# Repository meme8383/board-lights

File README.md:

# Meepo V3S ARGB Power & Control PCB
Schematic for Meepo V3S Skateboard Lights. Meant to power [these 24V WS2811 COB Leds](https://www.aliexpress.us/item/3256805848873454.html?gatewayAdapt=glo2usa) using the Meepo V3S 36V Battery and [wled firmware](https://kno.wled.ge/).

https://github.com/user-attachments/assets/10e10ca3-55f4-4bfa-9f18-f33567d93a93

## Known issues
This was my first real PCB project, so there were many (easily fixable) issues, but it still works as-is.
- Did not pull EN high (whoops). Bridge the two upper pins of the connector after the board is powered on.
- ESP-Prog connector is mirrored (whoops again).
- The output capacitor I planned to use did not support 24V. There is a capacitor with the same footprint and lower capacitance but higher max voltage that I used instead. Let me know if you want the full BOM.
- There is no power switch. I intented to use an inline waterproof switch on the connector, but it would have been nice to be able to disable the board without unplugging it or pulling the fuse.
- There are no holes (or space for them) to connect it to a mount.
- Level shifter did not work. I just bridged the pins and it works fine.

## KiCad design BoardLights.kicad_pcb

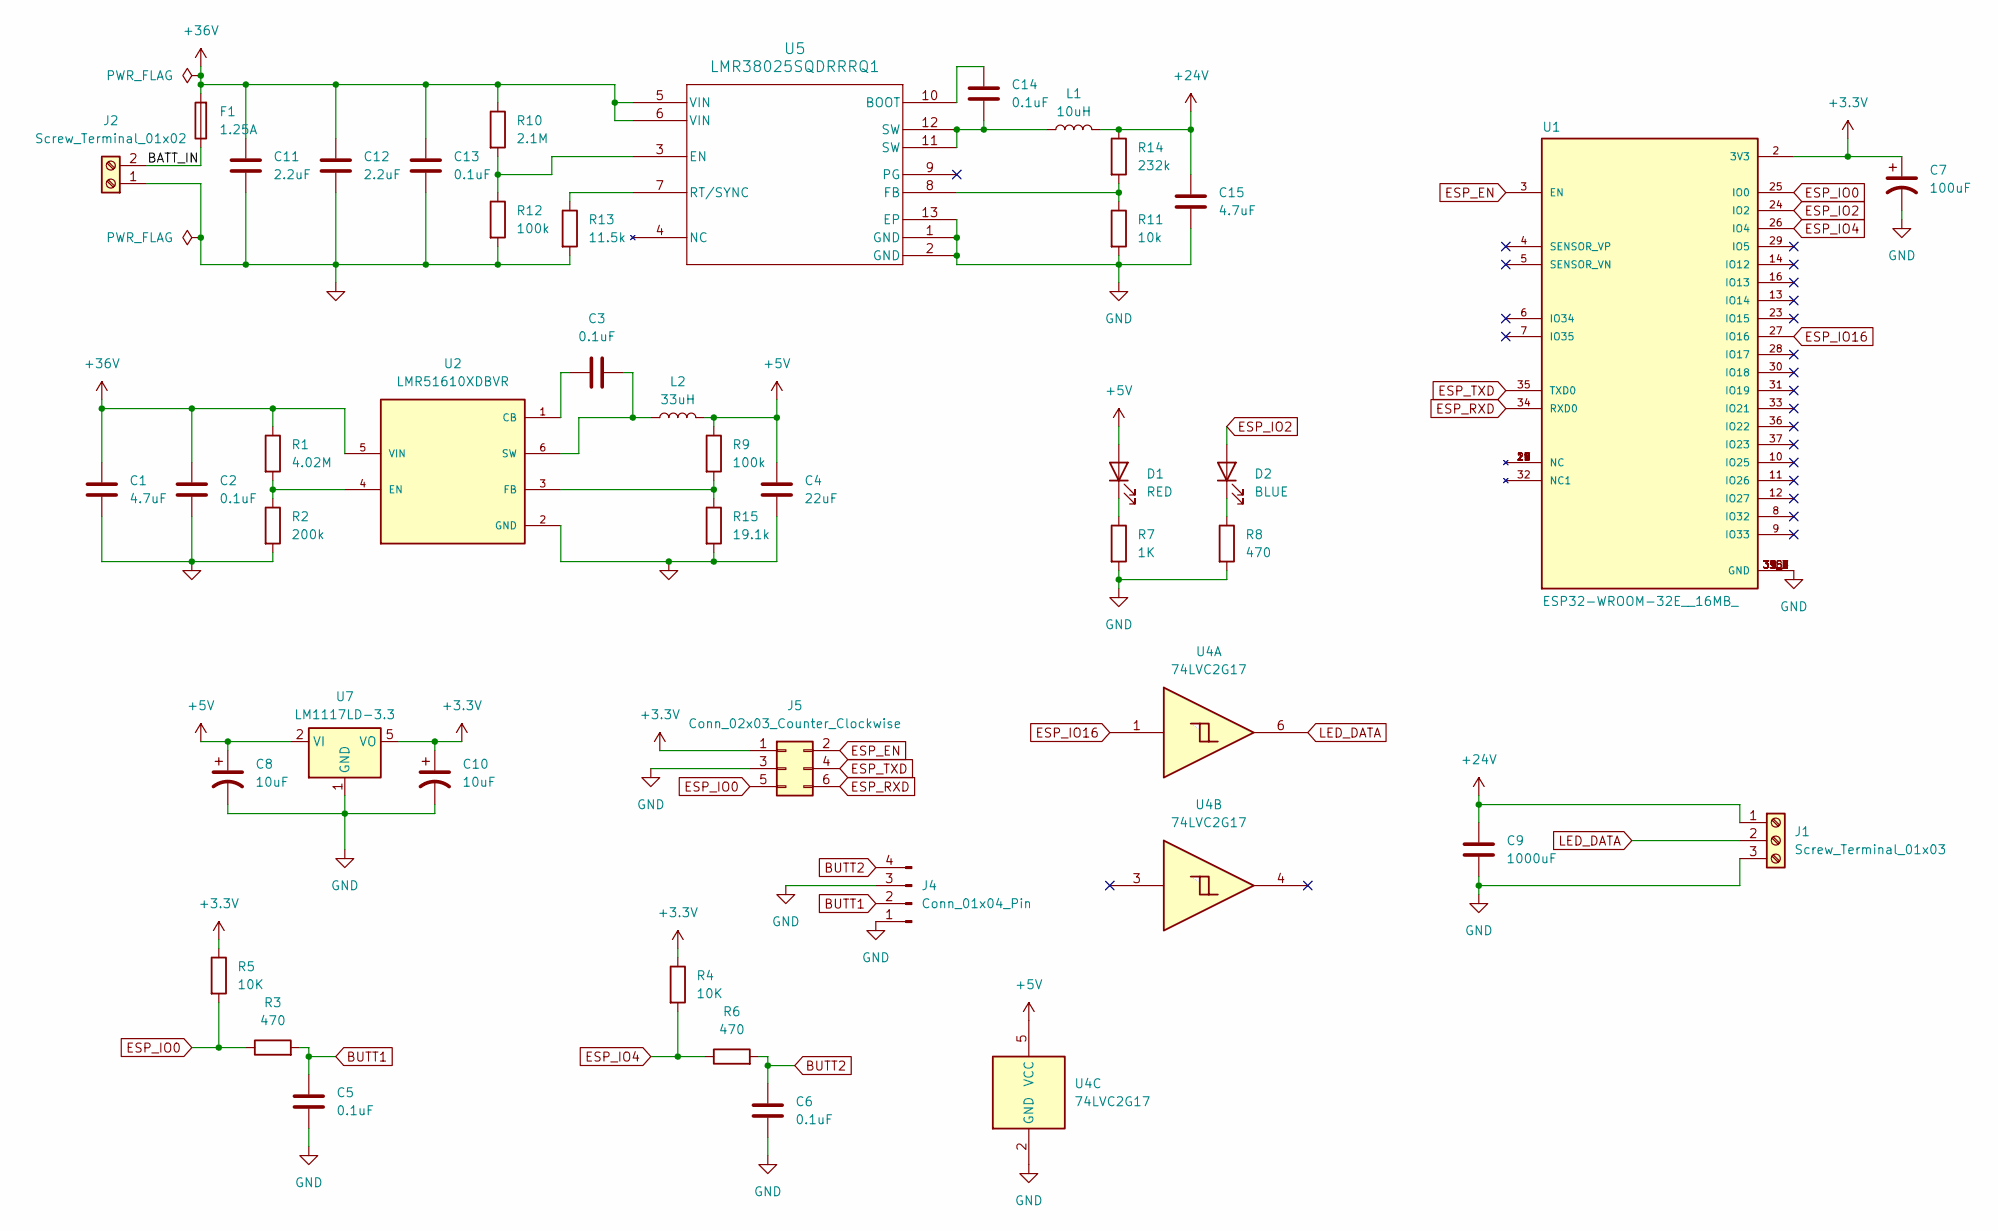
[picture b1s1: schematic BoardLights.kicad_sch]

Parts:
C1: 4.7uF; C_2220_5750Metric
C2: 0.1uF; C_0603_1608Metric
C3, C5, C6, C13, C14: 0.1uF; C_0402_1005Metric
C4: 22uF; C_0805_2012Metric
C7: 100uF; CP_EIA-7343-31_Kemet-D
C8, C10: 10uF; CP_EIA-3216-18_Kemet-A
C9: 1000uF; CAP_EEEFT1C102AP
C11, C12: 2.2uF; C_0805_2012Metric
C15: 4.7uF; C_1206_3216Metric
D1: RED; LED_0805_2012Metric
D2: BLUE; LED_0805_2012Metric
F1: 1.25A; FUSE_65600001009_LTF
J1: Screw_Terminal_01x03; TE_282841-3
J2: Screw_Terminal_01x02; TE_282841-2
J4: Conn_01x04_Pin; PinHeader_1x04_P2.54mm_Vertical
J5: Conn_02x03_Counter_Clockwise; TE_1761681-1
L1: 10uH; IND_IHLP-3232DZ_VIS
L2: 33uH; IND_IHLP-3232DZ_VIS
R1: 4.02M; R_0603_1608Metric
R2: 200k; R_0402_1005Metric
R3, R6, R8: 470; R_0402_1005Metric
R4, R5: 10K; R_0402_1005Metric
R7: 1K; R_0402_1005Metric
R9, R12: 100k; R_0402_1005Metric
R10: 2.1M; R_0402_1005Metric
R11: 10k; R_0402_1005Metric
R13: 11.5k; R_0402_1005Metric
R14: 232k; R_0402_1005Metric
R15: 19.1k; R_0402_1005Metric
U1: ESP32-WROOM-32E__16MB_; XCVR_ESP32-WROOM-32E__16MB_; PARTREV 1.4
U2: LMR51610XDBVR; SOT95P280X145-6N; PARTREV B
U4: 74LVC2G17; SOT95P280X145-6N
U5: LMR38025SQDRRRQ1; WSON12_DRR_TEX
U7: LM1117LD-3.3; DFN400X400X80-9N

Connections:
+3.3V: C7.1, C10.1, J5.1, R4.1, R5.1, U1.2 (3V3), U7.5 (VO), U7.6 (VO), U7.7 (VO), U7.9 (VO)
+5V: C4.2, C8.1, D1.2 (A), L2.2, R9.1, U4.5 (VCC), U7.2 (VI), U7.3 (VI), U7.4 (VI)
+24V: C9.1, C15.1, J1.1, L1.2, R14.1
+36V: C1.1, C2.1, C11.1, C12.1, C13.1, F1.2, R1.1, R10.1, U2.5 (VIN), U5.5 (VIN), U5.6 (VIN)
/BATT_IN: F1.1, J2.2
BUTT1: C5.1, J4.2, R3.2
BUTT2: C6.1, J4.4, R6.2
ESP_EN: J5.2, U1.3 (EN)
ESP_IO0: J5.5, R3.1, R5.2, U1.25 (IO0)
ESP_IO2: D2.2 (A), U1.24 (IO2)
ESP_IO4: R4.2, R6.1, U1.26 (IO4)
ESP_IO16: U1.27 (IO16), U4.1
ESP_RXD: J5.6, U1.34 (RXD0)
ESP_TXD: J5.4, U1.35 (TXD0)
GND: C1.2, C2.2, C4.1, C5.2, C6.2, C7.2, C8.2, C9.2, C10.2, C11.2, C12.2, C13.2, C15.2, J1.3, J2.1, J4.1, J4.3, J5.3, R2.2, R7.2, R8.2, R11.2, R12.2, R13.2, R15.2, U1.1 (GND), U1.15 (GND), U1.38 (GND), U1.39_1 (GND), U1.39_2 (GND), U1.39_3 (GND), U1.39_4 (GND), U1.39_5 (GND), U1.39_6 (GND), U1.39_7 (GND), U1.39_8 (GND), U1.39_9 (GND), U2.2 (GND), U4.2 (GND), U5.1 (GND), U5.2 (GND), U5.13 (EP), U7.1 (GND)
LED_DATA: J1.2, U4.6
unnamed: C14.2, L1.1, U5.11 (SW), U5.12 (SW)
unnamed: D1.1 (K), R7.1
unnamed: D2.1 (K), R8.1
unnamed: C3.1, U2.1 (CB)
unnamed: R1.2, R2.1, U2.4 (EN)
unnamed: R9.2, R15.1, U2.3 (FB)
unnamed: C3.2, L2.1, U2.6 (SW)
unnamed: C14.1, U5.10 (BOOT)
unnamed: R10.2, R12.1, U5.3 (EN)
unnamed: R11.1, R14.2, U5.8 (FB)
unnamed: R13.1, U5.7 (RT/SYNC)

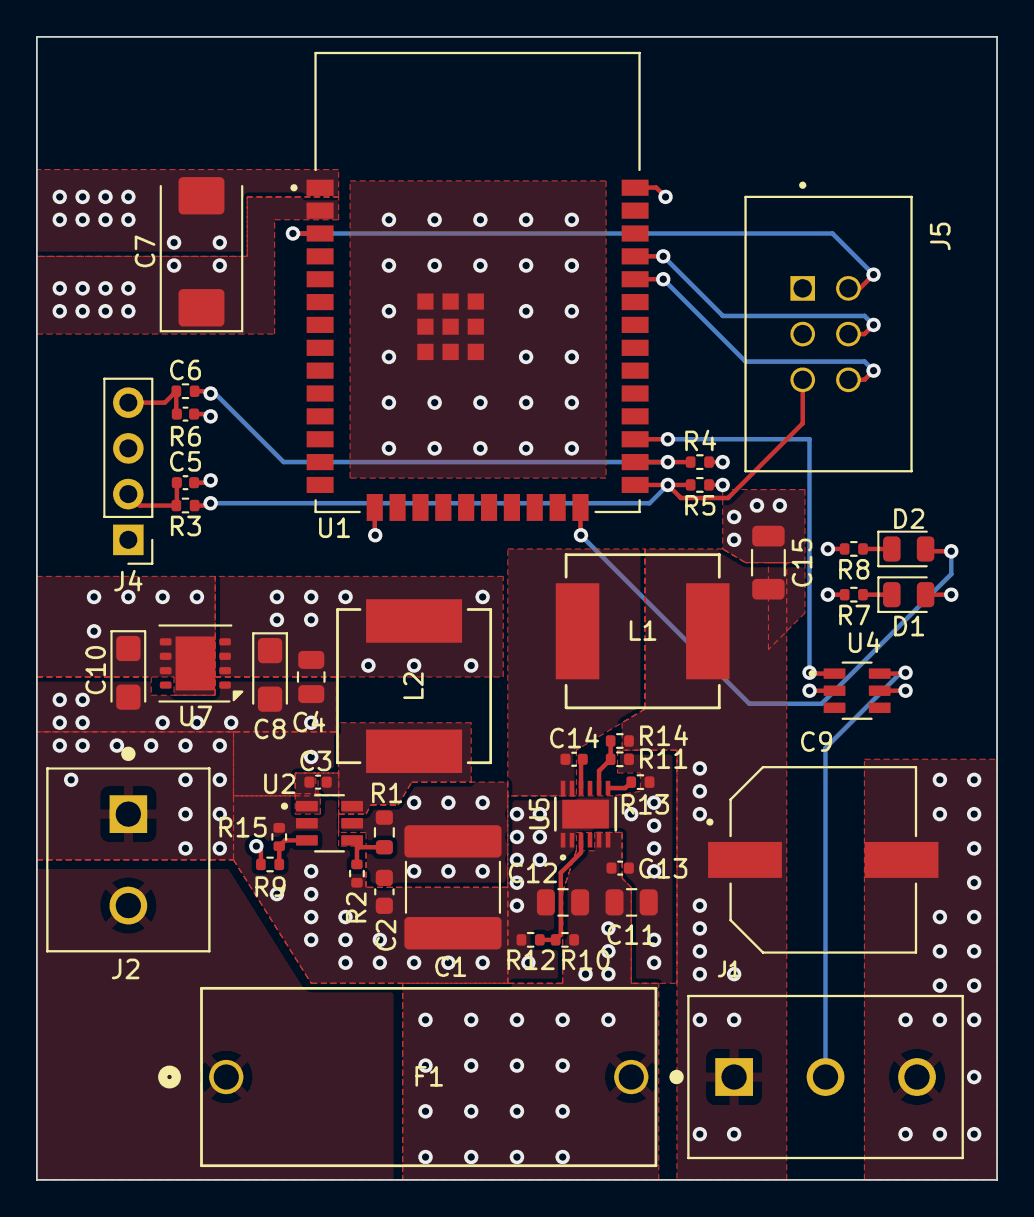
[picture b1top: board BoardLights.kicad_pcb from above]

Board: 4 copper layers, 53.3 x 63.5 mm, 44 parts (0 on the bottom side), 27 nets.

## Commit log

2024-11-13 Add visuals
